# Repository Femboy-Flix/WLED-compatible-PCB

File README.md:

# WLED-compatible-PCB
A cheep PCB to use an ESP(super mini) for WLED

Here you fine the full kicad Projeckt to order your one version or improve 
You can just clone the repositorie and open the {W-LED.kicad_pro} file (you need to have kicad installd)
If you want to order from JLC PCB (I recomend), i havew the fabricaton-toolkit exported files in the production folder. you can uloud them direcktly to JLC PCB 

the STL files are also on Printables (https://www.printables.com/model/1768994-esp-x-super-mini-pcb-wled)

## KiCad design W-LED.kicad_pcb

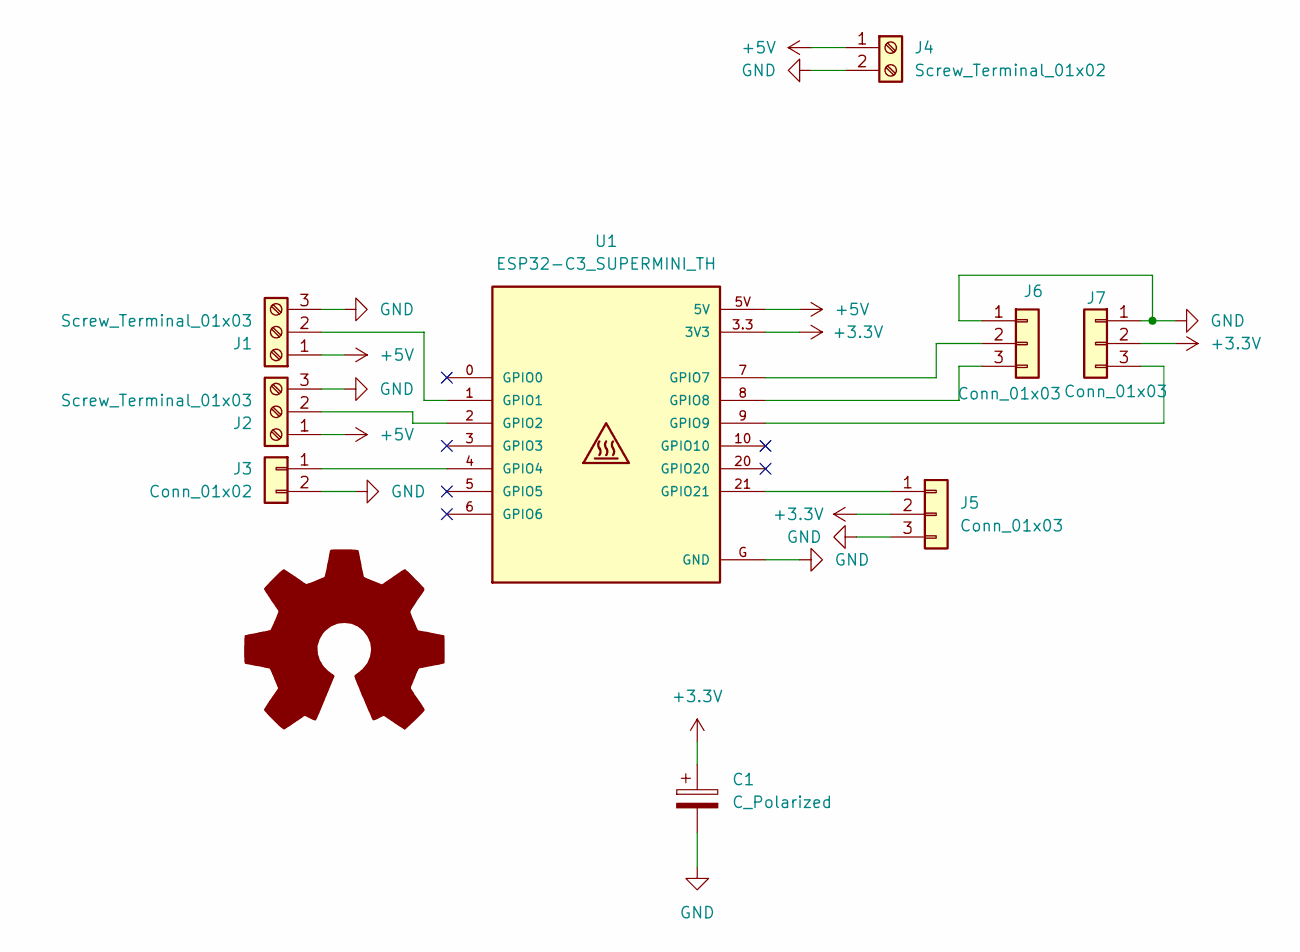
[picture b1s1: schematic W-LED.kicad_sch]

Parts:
C1: C_Polarized; CP_Radial_D4.0mm_P2.00mm
J1, J2: Screw_Terminal_01x03; PinHeader_1x03_P2.54mm_Vertical
J3: Conn_01x02; PinHeader_1x02_P2.54mm_Vertical
J4: Screw_Terminal_01x02; PinHeader_1x02_P2.54mm_Vertical
J5, J6, J7: Conn_01x03; PinHeader_1x03_P2.54mm_Vertical
U1: ESP32-C3_SUPERMINI_TH; MODULE_ESP32-C3_SUPERMINI_TH

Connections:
+3.3V: C1.1, J5.2, J7.2, U1.3.3 (3V3)
+5V: J1.1, J2.1, J4.1, U1.5V
GND: C1.2, J1.3, J2.3, J3.2, J4.2, J5.3, J6.1, J7.1, U1.G (GND)
unnamed: J1.2, U1.1 (GPIO1)
unnamed: J2.2, U1.2 (GPIO2)
unnamed: J3.1, U1.4 (GPIO4)
unnamed: J5.1, U1.21 (GPIO21)
unnamed: J6.2, U1.7 (GPIO7)
unnamed: J6.3, U1.8 (GPIO8)
unnamed: J7.3, U1.9 (GPIO9)

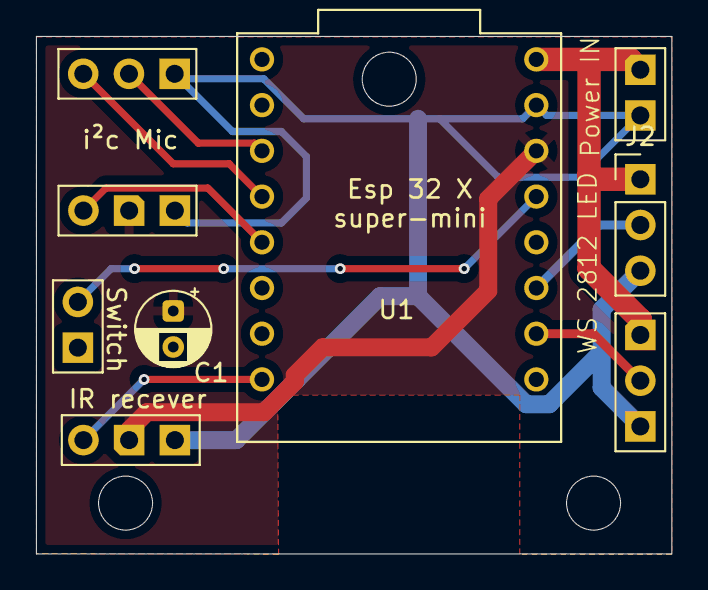
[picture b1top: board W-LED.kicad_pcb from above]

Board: 2 copper layers, 35.3 x 28.8 mm, 9 parts (0 on the bottom side), 10 nets.

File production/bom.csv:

Designator,Footprint,Quantity,Value,LCSC Part #
C1,CP_Radial_D4.0mm_P2.00mm,1,C_Polarized,
"J1, J2",PinHeader_1x03_P2.54mm_Vertical,2,Screw_Terminal_01x03,
J3,PinHeader_1x02_P2.54mm_Vertical,1,Conn_01x02,
J4,PinHeader_1x02_P2.54mm_Vertical,1,Screw_Terminal_01x02,
"J5, J6, J7",PinHeader_1x03_P2.54mm_Vertical,3,Conn_01x03,
U1,MODULE_ESP32-C3_SUPERMINI_TH,1,ESP32-C3_SUPERMINI_TH,
